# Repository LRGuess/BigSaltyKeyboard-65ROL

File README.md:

# BigSaltyKeyboard-65ROL
A 65% Keyboard with a rotary encoder, OLED screen and LEDs

## BOM:

- 1x Raspberry Pi Pico
- 68x Cheery MX Switches and their keycaps
- 68x [1N4148 Through-Hole Diodes](https://www.digikey.ca/en/products/detail/onsemi/1N4148/458603)
- 1x 6.25u Stabilizer
- 2x 2.25u Stabilizer
- 1x 2u Stabilizer
- 68x [SK6812 MINI-E LEDs](https://www.lcsc.com/product-detail/C5149201.html)
- 1x [Logic Level Shifter](https://www.digikey.ca/en/products/detail/texas-instruments/SN74AHCT1G125DBVR/376028)
- 69x [0.1 µF Chip Capacitor](https://www.digikey.ca/en/products/detail/samsung-electro-mechanics/CL05B104KP5VPNC/20498482)
- 1x [500 OHM Chip Resistor](https://www.digikey.ca/en/products/detail/yageo/RT0603BRC07500RL/7708292)
- 2x [10 Pin Horizontal Header](https://www.digikey.ca/en/products/detail/w%C3%BCrth-elektronik/61301011021/2508443)

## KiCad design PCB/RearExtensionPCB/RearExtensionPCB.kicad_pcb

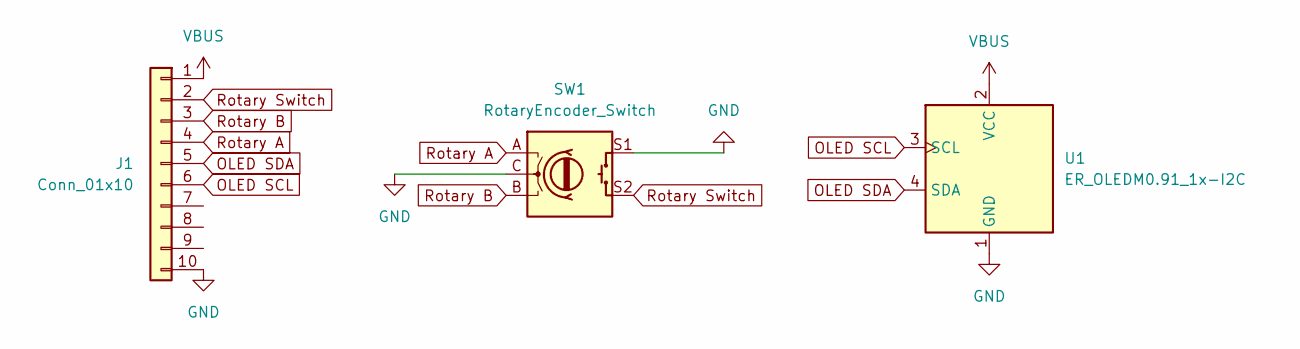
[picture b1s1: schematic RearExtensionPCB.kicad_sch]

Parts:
J1: Conn_01x10; PinHeader_1x10_P2.54mm_Horizontal
SW1: RotaryEncoder_Switch; RotaryEncoder_Alps_EC11E-Switch_Vertical_H20mm
U1: ER_OLEDM0.91_1x-I2C

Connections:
GND: J1.10, SW1.C, SW1.S1, U1.1 (GND)
OLED SCL: J1.6, U1.3 (SCL)
OLED SDA: J1.5, U1.4 (SDA)
Rotary A: J1.4, SW1.A
Rotary B: J1.3, SW1.B
Rotary Switch: J1.2, SW1.S2
VBUS: J1.1, U1.2 (VCC)

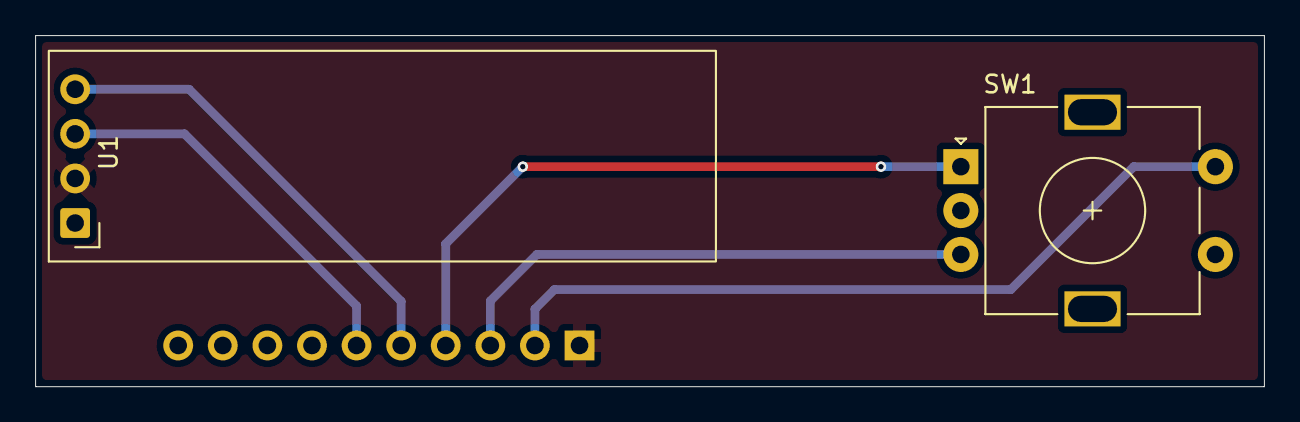
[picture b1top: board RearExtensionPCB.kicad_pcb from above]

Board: 2 copper layers, 70.0 x 20.0 mm, 3 parts (1 on the bottom side), 7 nets.

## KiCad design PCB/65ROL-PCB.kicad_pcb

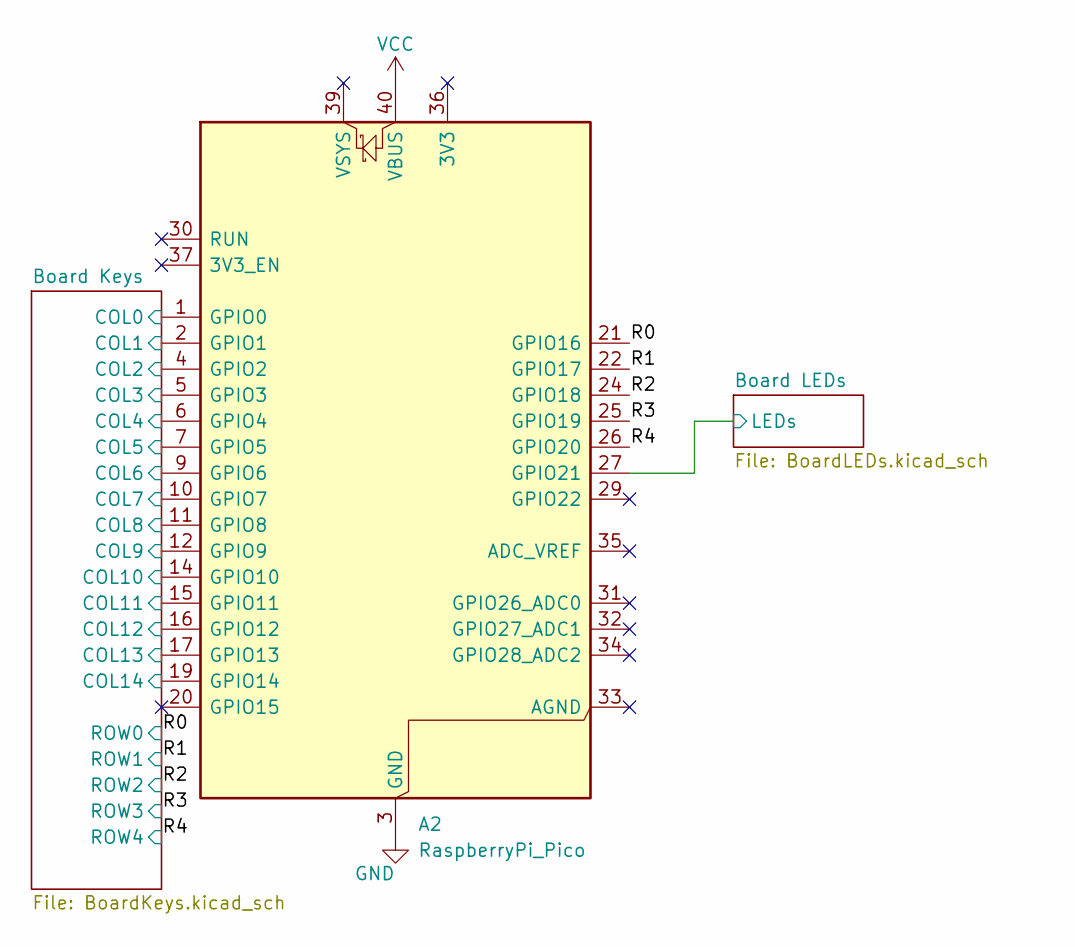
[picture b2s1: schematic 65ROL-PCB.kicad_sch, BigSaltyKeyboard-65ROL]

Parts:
A2: RaspberryPi_Pico; RaspberryPi_Pico_Common_THT

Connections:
/Board Keys/COL0: A2.1 (GPIO0); also elsewhere on the board
/Board Keys/COL1: A2.2 (GPIO1); also elsewhere on the board
/Board Keys/COL2: A2.4 (GPIO2); also elsewhere on the board
/Board Keys/COL3: A2.5 (GPIO3); also elsewhere on the board
/Board Keys/COL4: A2.6 (GPIO4); also elsewhere on the board
/Board Keys/COL5: A2.7 (GPIO5); also elsewhere on the board
/Board Keys/COL6: A2.9 (GPIO6); also elsewhere on the board
/Board Keys/COL7: A2.10 (GPIO7); also elsewhere on the board
/Board Keys/COL8: A2.11 (GPIO8); also elsewhere on the board
/Board Keys/COL9: A2.12 (GPIO9); also elsewhere on the board
/Board Keys/COL10: A2.14 (GPIO10); also elsewhere on the board
/Board Keys/COL11: A2.15 (GPIO11); also elsewhere on the board
/Board Keys/COL12: A2.16 (GPIO12); also elsewhere on the board
/Board Keys/COL13: A2.17 (GPIO13); also elsewhere on the board
/Board Keys/COL14: A2.19 (GPIO14); also elsewhere on the board
/Board LEDs/LEDs: A2.27 (GPIO21); also elsewhere on the board
/R0: A2.21 (GPIO16); also elsewhere on the board
/R1: A2.22 (GPIO17); also elsewhere on the board
/R2: A2.24 (GPIO18); also elsewhere on the board
/R3: A2.25 (GPIO19); also elsewhere on the board
/R4: A2.26 (GPIO20); also elsewhere on the board
GND: A2.3 (GND), A2.8 (GND), A2.13 (GND), A2.18 (GND), A2.23 (GND), A2.28 (GND), A2.38 (GND); also elsewhere on the board
VCC: A2.40 (VBUS); also elsewhere on the board

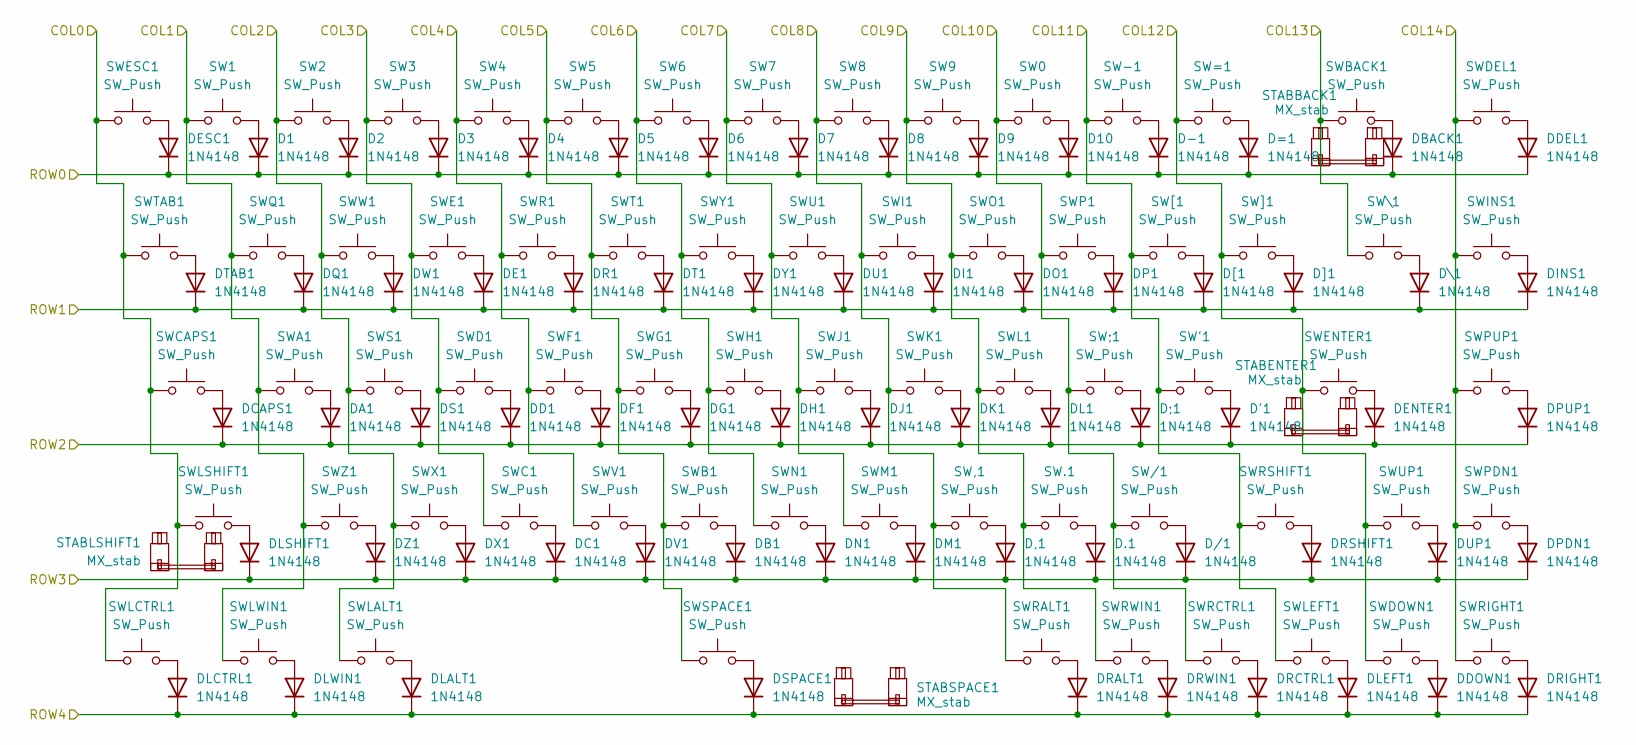
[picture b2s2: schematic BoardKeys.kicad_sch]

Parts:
D1, D2, D3, D4, D5, D6, D7, D8, D9, D10, D.1: 1N4148; D_DO-35_SOD27_P7.62mm_Horizontal
D'1: 1N4148; D_DO-35_SOD27_P7.62mm_Horizontal
D,1: 1N4148; D_DO-35_SOD27_P7.62mm_Horizontal
D-1: 1N4148; D_DO-35_SOD27_P7.62mm_Horizontal
D/1: 1N4148; D_DO-35_SOD27_P7.62mm_Horizontal
D;1: 1N4148; D_DO-35_SOD27_P7.62mm_Horizontal
D=1: 1N4148; D_DO-35_SOD27_P7.62mm_Horizontal
DA1: 1N4148; D_DO-35_SOD27_P7.62mm_Horizontal
DB1: 1N4148; D_DO-35_SOD27_P7.62mm_Horizontal
DBACK1: 1N4148; D_DO-35_SOD27_P7.62mm_Horizontal
DC1: 1N4148; D_DO-35_SOD27_P7.62mm_Horizontal
DCAPS1: 1N4148; D_DO-35_SOD27_P7.62mm_Horizontal
DD1: 1N4148; D_DO-35_SOD27_P7.62mm_Horizontal
DDEL1: 1N4148; D_DO-35_SOD27_P7.62mm_Horizontal
DDOWN1: 1N4148; D_DO-35_SOD27_P7.62mm_Horizontal
DE1: 1N4148; D_DO-35_SOD27_P7.62mm_Horizontal
DENTER1: 1N4148; D_DO-35_SOD27_P7.62mm_Horizontal
DESC1: 1N4148; D_DO-35_SOD27_P7.62mm_Horizontal
DF1: 1N4148; D_DO-35_SOD27_P7.62mm_Horizontal
DG1: 1N4148; D_DO-35_SOD27_P7.62mm_Horizontal
DH1: 1N4148; D_DO-35_SOD27_P7.62mm_Horizontal
DI1: 1N4148; D_DO-35_SOD27_P7.62mm_Horizontal
DINS1: 1N4148; D_DO-35_SOD27_P7.62mm_Horizontal
DJ1: 1N4148; D_DO-35_SOD27_P7.62mm_Horizontal
DK1: 1N4148; D_DO-35_SOD27_P7.62mm_Horizontal
DL1: 1N4148; D_DO-35_SOD27_P7.62mm_Horizontal
DLALT1: 1N4148; D_DO-35_SOD27_P7.62mm_Horizontal
DLCTRL1: 1N4148; D_DO-35_SOD27_P7.62mm_Horizontal
DLEFT1: 1N4148; D_DO-35_SOD27_P7.62mm_Horizontal
DLSHIFT1: 1N4148; D_DO-35_SOD27_P7.62mm_Horizontal
DLWIN1: 1N4148; D_DO-35_SOD27_P7.62mm_Horizontal
DM1: 1N4148; D_DO-35_SOD27_P7.62mm_Horizontal
DN1: 1N4148; D_DO-35_SOD27_P7.62mm_Horizontal
DO1: 1N4148; D_DO-35_SOD27_P7.62mm_Horizontal
DP1: 1N4148; D_DO-35_SOD27_P7.62mm_Horizontal
DPDN1: 1N4148; D_DO-35_SOD27_P7.62mm_Horizontal
DPUP1: 1N4148; D_DO-35_SOD27_P7.62mm_Horizontal
DQ1: 1N4148; D_DO-35_SOD27_P7.62mm_Horizontal
DR1: 1N4148; D_DO-35_SOD27_P7.62mm_Horizontal
DRALT1: 1N4148; D_DO-35_SOD27_P7.62mm_Horizontal
DRCTRL1: 1N4148; D_DO-35_SOD27_P7.62mm_Horizontal
DRIGHT1: 1N4148; D_DO-35_SOD27_P7.62mm_Horizontal
DRSHIFT1: 1N4148; D_DO-35_SOD27_P7.62mm_Horizontal
DRWIN1: 1N4148; D_DO-35_SOD27_P7.62mm_Horizontal
DS1: 1N4148; D_DO-35_SOD27_P7.62mm_Horizontal
DSPACE1: 1N4148; D_DO-35_SOD27_P7.62mm_Horizontal
DT1: 1N4148; D_DO-35_SOD27_P7.62mm_Horizontal
DTAB1: 1N4148; D_DO-35_SOD27_P7.62mm_Horizontal
DU1: 1N4148; D_DO-35_SOD27_P7.62mm_Horizontal
DUP1: 1N4148; D_DO-35_SOD27_P7.62mm_Horizontal
DV1: 1N4148; D_DO-35_SOD27_P7.62mm_Horizontal
DW1: 1N4148; D_DO-35_SOD27_P7.62mm_Horizontal
DX1: 1N4148; D_DO-35_SOD27_P7.62mm_Horizontal
DY1: 1N4148; D_DO-35_SOD27_P7.62mm_Horizontal
DZ1: 1N4148; D_DO-35_SOD27_P7.62mm_Horizontal
D[1: 1N4148; D_DO-35_SOD27_P7.62mm_Horizontal
D\1: 1N4148; D_DO-35_SOD27_P7.62mm_Horizontal
D]1: 1N4148; D_DO-35_SOD27_P7.62mm_Horizontal
STABBACK1: MX_stab; STAB_MX_2u
STABENTER1: MX_stab; STAB_MX_2.25u
STABLSHIFT1: MX_stab; STAB_MX_2.25u
STABSPACE1: MX_stab; STAB_MX_6.25u
SW0, SW1, SW2, SW3, SW4, SW5, SW6, SW7, SW8, SW9, SW.1: SW_Push; SW_MX_1u
SW'1: SW_Push; SW_MX_1u
SW,1: SW_Push; SW_MX_1u
SW-1: SW_Push; SW_MX_1u
SW/1: SW_Push; SW_MX_1u
SW;1: SW_Push; SW_MX_1u
SW=1: SW_Push; SW_MX_1u
SWA1: SW_Push; SW_MX_1u
SWB1: SW_Push; SW_MX_1u
SWBACK1: SW_Push; SW_MX_1u
SWC1: SW_Push; SW_MX_1u
SWCAPS1: SW_Push; SW_MX_1u
SWD1: SW_Push; SW_MX_1u
SWDEL1: SW_Push; SW_MX_1u
SWDOWN1: SW_Push; SW_MX_1u
SWE1: SW_Push; SW_MX_1u
SWENTER1: SW_Push; SW_MX_1u
SWESC1: SW_Push; SW_MX_1u
SWF1: SW_Push; SW_MX_1u
SWG1: SW_Push; SW_MX_1u
SWH1: SW_Push; SW_MX_1u
SWI1: SW_Push; SW_MX_1u
SWINS1: SW_Push; SW_MX_1u
SWJ1: SW_Push; SW_MX_1u
SWK1: SW_Push; SW_MX_1u
SWL1: SW_Push; SW_MX_1u
SWLALT1: SW_Push; SW_MX_1u
SWLCTRL1: SW_Push; SW_MX_1u
SWLEFT1: SW_Push; SW_MX_1u
SWLSHIFT1: SW_Push; SW_MX_1u
SWLWIN1: SW_Push; SW_MX_1u
SWM1: SW_Push; SW_MX_1u
SWN1: SW_Push; SW_MX_1u
SWO1: SW_Push; SW_MX_1u
SWP1: SW_Push; SW_MX_1u
SWPDN1: SW_Push; SW_MX_1u
SWPUP1: SW_Push; SW_MX_1u
SWQ1: SW_Push; SW_MX_1u
SWR1: SW_Push; SW_MX_1u
SWRALT1: SW_Push; SW_MX_1u
SWRCTRL1: SW_Push; SW_MX_1u
SWRIGHT1: SW_Push; SW_MX_1u
SWRSHIFT1: SW_Push; SW_MX_1u
SWRWIN1: SW_Push; SW_MX_1u
SWS1: SW_Push; SW_MX_1u
SWSPACE1: SW_Push; SW_MX_1u
SWT1: SW_Push; SW_MX_1u
SWTAB1: SW_Push; SW_MX_1u
SWU1: SW_Push; SW_MX_1u
SWUP1: SW_Push; SW_MX_1u
SWV1: SW_Push; SW_MX_1u
SWW1: SW_Push; SW_MX_1u
SWX1: SW_Push; SW_MX_1u
SWY1: SW_Push; SW_MX_1u
SWZ1: SW_Push; SW_MX_1u
SW[1: SW_Push; SW_MX_1u
SW\1: SW_Push; SW_MX_1u
SW]1: SW_Push; SW_MX_1u

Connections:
/Board Keys/COL0: SWCAPS1.1, SWESC1.1, SWLCTRL1.1, SWLSHIFT1.1, SWTAB1.1; also elsewhere on the board
/Board Keys/COL1: SW1.1, SWA1.1, SWLWIN1.1, SWQ1.1, SWZ1.1; also elsewhere on the board
/Board Keys/COL2: SW2.1, SWLALT1.1, SWS1.1, SWW1.1, SWX1.1; also elsewhere on the board
/Board Keys/COL3: SW3.1, SWC1.1, SWD1.1, SWE1.1; also elsewhere on the board
/Board Keys/COL4: SW4.1, SWF1.1, SWR1.1, SWV1.1; also elsewhere on the board
/Board Keys/COL5: SW5.1, SWB1.1, SWG1.1, SWSPACE1.1, SWT1.1; also elsewhere on the board
/Board Keys/COL6: SW6.1, SWH1.1, SWN1.1, SWY1.1; also elsewhere on the board
/Board Keys/COL7: SW7.1, SWJ1.1, SWM1.1, SWU1.1; also elsewhere on the board
/Board Keys/COL8: SW8.1, SW,1.1, SWI1.1, SWK1.1, SWRALT1.1; also elsewhere on the board
/Board Keys/COL9: SW9.1, SW.1.1, SWL1.1, SWO1.1, SWRWIN1.1; also elsewhere on the board
/Board Keys/COL10: SW0.1, SW/1.1, SW;1.1, SWP1.1, SWRCTRL1.1; also elsewhere on the board
/Board Keys/COL11: SW'1.1, SW-1.1, SWLEFT1.1, SWRSHIFT1.1, SW[1.1; also elsewhere on the board
/Board Keys/COL12: SW=1.1, SWDOWN1.1, SWENTER1.1, SWUP1.1, SW]1.1; also elsewhere on the board
/Board Keys/COL13: SWBACK1.1, SW\1.1; also elsewhere on the board
/Board Keys/COL14: SWDEL1.1, SWINS1.1, SWPDN1.1, SWPUP1.1, SWRIGHT1.1; also elsewhere on the board
/R0: D1.1 (K), D2.1 (K), D3.1 (K), D4.1 (K), D5.1 (K), D6.1 (K), D7.1 (K), D8.1 (K), D9.1 (K), D10.1 (K), D-1.1 (K), D=1.1 (K), DBACK1.1 (K), DDEL1.1 (K), DESC1.1 (K); also elsewhere on the board
/R1: DE1.1 (K), DI1.1 (K), DINS1.1 (K), DO1.1 (K), DP1.1 (K), DQ1.1 (K), DR1.1 (K), DT1.1 (K), DTAB1.1 (K), DU1.1 (K), DW1.1 (K), DY1.1 (K), D[1.1 (K), D\1.1 (K), D]1.1 (K); also elsewhere on the board
/R2: D'1.1 (K), D;1.1 (K), DA1.1 (K), DCAPS1.1 (K), DD1.1 (K), DENTER1.1 (K), DF1.1 (K), DG1.1 (K), DH1.1 (K), DJ1.1 (K), DK1.1 (K), DL1.1 (K), DPUP1.1 (K), DS1.1 (K); also elsewhere on the board
/R3: D,1.1 (K), D.1.1 (K), D/1.1 (K), DB1.1 (K), DC1.1 (K), DLSHIFT1.1 (K), DM1.1 (K), DN1.1 (K), DPDN1.1 (K), DRSHIFT1.1 (K), DUP1.1 (K), DV1.1 (K), DX1.1 (K), DZ1.1 (K); also elsewhere on the board
/R4: DDOWN1.1 (K), DLALT1.1 (K), DLCTRL1.1 (K), DLEFT1.1 (K), DLWIN1.1 (K), DRALT1.1 (K), DRCTRL1.1 (K), DRIGHT1.1 (K), DRWIN1.1 (K), DSPACE1.1 (K); also elsewhere on the board
unnamed: D1.2 (A), SW1.2
unnamed: D2.2 (A), SW2.2
unnamed: D3.2 (A), SW3.2
unnamed: D4.2 (A), SW4.2
unnamed: D5.2 (A), SW5.2
unnamed: D6.2 (A), SW6.2
unnamed: D7.2 (A), SW7.2
unnamed: D8.2 (A), SW8.2
unnamed: D9.2 (A), SW9.2
unnamed: D10.2 (A), SW0.2
unnamed: D'1.2 (A), SW'1.2
unnamed: D,1.2 (A), SW,1.2
unnamed: D-1.2 (A), SW-1.2
unnamed: D.1.2 (A), SW.1.2
unnamed: D/1.2 (A), SW/1.2
unnamed: D;1.2 (A), SW;1.2
unnamed: D=1.2 (A), SW=1.2
unnamed: DA1.2 (A), SWA1.2
unnamed: DB1.2 (A), SWB1.2
unnamed: DBACK1.2 (A), SWBACK1.2
unnamed: DC1.2 (A), SWC1.2
unnamed: DCAPS1.2 (A), SWCAPS1.2
unnamed: DD1.2 (A), SWD1.2
unnamed: DDEL1.2 (A), SWDEL1.2
unnamed: DDOWN1.2 (A), SWDOWN1.2
unnamed: DE1.2 (A), SWE1.2
unnamed: DENTER1.2 (A), SWENTER1.2
unnamed: DESC1.2 (A), SWESC1.2
unnamed: DF1.2 (A), SWF1.2
unnamed: DG1.2 (A), SWG1.2
unnamed: DH1.2 (A), SWH1.2
unnamed: DI1.2 (A), SWI1.2
unnamed: DINS1.2 (A), SWINS1.2
unnamed: DJ1.2 (A), SWJ1.2
unnamed: DK1.2 (A), SWK1.2
unnamed: DL1.2 (A), SWL1.2
unnamed: DLALT1.2 (A), SWLALT1.2
unnamed: DLCTRL1.2 (A), SWLCTRL1.2
unnamed: DLEFT1.2 (A), SWLEFT1.2
unnamed: DLSHIFT1.2 (A), SWLSHIFT1.2
unnamed: DLWIN1.2 (A), SWLWIN1.2
unnamed: DM1.2 (A), SWM1.2
unnamed: DN1.2 (A), SWN1.2
unnamed: DO1.2 (A), SWO1.2
unnamed: DP1.2 (A), SWP1.2
unnamed: DPDN1.2 (A), SWPDN1.2
unnamed: DPUP1.2 (A), SWPUP1.2
unnamed: DQ1.2 (A), SWQ1.2
unnamed: DR1.2 (A), SWR1.2
unnamed: DRALT1.2 (A), SWRALT1.2
unnamed: DRCTRL1.2 (A), SWRCTRL1.2
unnamed: DRIGHT1.2 (A), SWRIGHT1.2
unnamed: DRSHIFT1.2 (A), SWRSHIFT1.2
unnamed: DRWIN1.2 (A), SWRWIN1.2
unnamed: DS1.2 (A), SWS1.2
unnamed: DSPACE1.2 (A), SWSPACE1.2
unnamed: DT1.2 (A), SWT1.2
unnamed: DTAB1.2 (A), SWTAB1.2
unnamed: DU1.2 (A), SWU1.2
unnamed: DUP1.2 (A), SWUP1.2
unnamed: DV1.2 (A), SWV1.2
unnamed: DW1.2 (A), SWW1.2
unnamed: DX1.2 (A), SWX1.2
unnamed: DY1.2 (A), SWY1.2
unnamed: DZ1.2 (A), SWZ1.2
unnamed: D[1.2 (A), SW[1.2
unnamed: D\1.2 (A), SW\1.2
unnamed: D]1.2 (A), SW]1.2

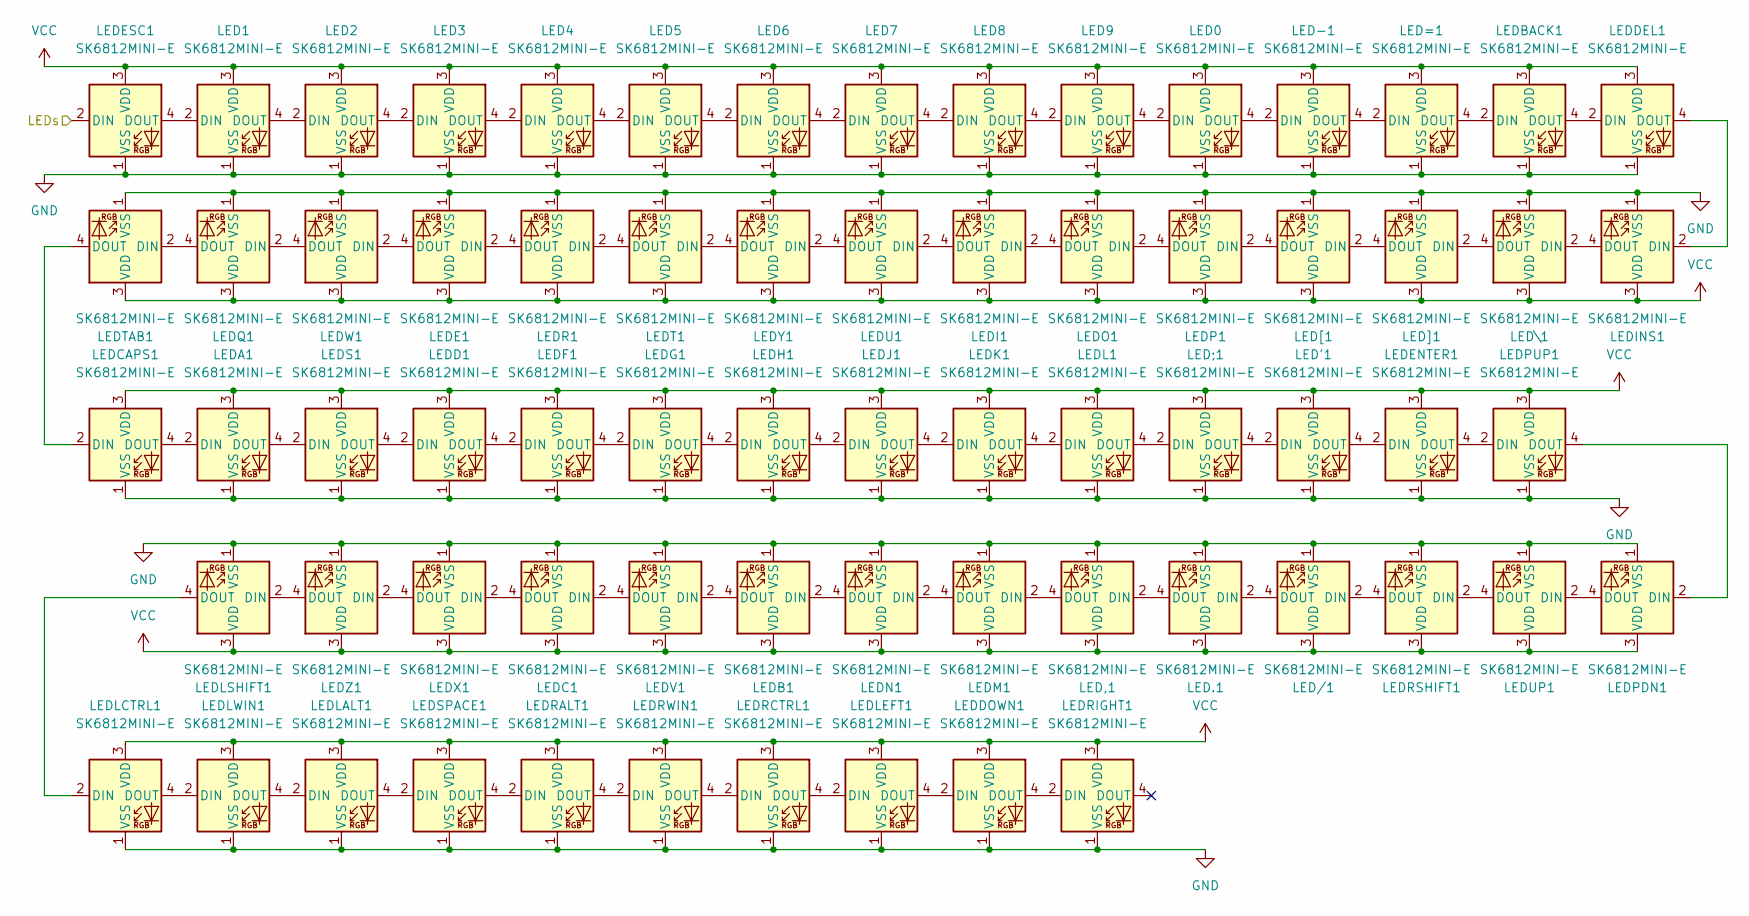
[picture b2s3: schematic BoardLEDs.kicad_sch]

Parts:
LED0, LED1, LED2, LED3, LED4, LED5, LED6, LED7, LED8, LED9, LED.1: SK6812MINI-E; SK6812MINI-E_fixed
LED'1: SK6812MINI-E; SK6812MINI-E_fixed
LED,1: SK6812MINI-E; SK6812MINI-E_fixed
LED-1: SK6812MINI-E; SK6812MINI-E_fixed
LED/1: SK6812MINI-E; SK6812MINI-E_fixed
LED;1: SK6812MINI-E; SK6812MINI-E_fixed
LED=1: SK6812MINI-E; SK6812MINI-E_fixed
LEDA1: SK6812MINI-E; SK6812MINI-E_fixed
LEDB1: SK6812MINI-E; SK6812MINI-E_fixed
LEDBACK1: SK6812MINI-E; SK6812MINI-E_fixed
LEDC1: SK6812MINI-E; SK6812MINI-E_fixed
LEDCAPS1: SK6812MINI-E; SK6812MINI-E_fixed
LEDD1: SK6812MINI-E; SK6812MINI-E_fixed
LEDDEL1: SK6812MINI-E; SK6812MINI-E_fixed
LEDDOWN1: SK6812MINI-E; SK6812MINI-E_fixed
LEDE1: SK6812MINI-E; SK6812MINI-E_fixed
LEDENTER1: SK6812MINI-E; SK6812MINI-E_fixed
LEDESC1: SK6812MINI-E; SK6812MINI-E_fixed
LEDF1: SK6812MINI-E; SK6812MINI-E_fixed
LEDG1: SK6812MINI-E; SK6812MINI-E_fixed
LEDH1: SK6812MINI-E; SK6812MINI-E_fixed
LEDI1: SK6812MINI-E; SK6812MINI-E_fixed
LEDINS1: SK6812MINI-E; SK6812MINI-E_fixed
LEDJ1: SK6812MINI-E; SK6812MINI-E_fixed
LEDK1: SK6812MINI-E; SK6812MINI-E_fixed
LEDL1: SK6812MINI-E; SK6812MINI-E_fixed
LEDLALT1: SK6812MINI-E; SK6812MINI-E_fixed
LEDLCTRL1: SK6812MINI-E; SK6812MINI-E_fixed
LEDLEFT1: SK6812MINI-E; SK6812MINI-E_fixed
LEDLSHIFT1: SK6812MINI-E; SK6812MINI-E_fixed
LEDLWIN1: SK6812MINI-E; SK6812MINI-E_fixed
LEDM1: SK6812MINI-E; SK6812MINI-E_fixed
LEDN1: SK6812MINI-E; SK6812MINI-E_fixed
LEDO1: SK6812MINI-E; SK6812MINI-E_fixed
LEDP1: SK6812MINI-E; SK6812MINI-E_fixed
LEDPDN1: SK6812MINI-E; SK6812MINI-E_fixed
LEDPUP1: SK6812MINI-E; SK6812MINI-E_fixed
LEDQ1: SK6812MINI-E; SK6812MINI-E_fixed
LEDR1: SK6812MINI-E; SK6812MINI-E_fixed
LEDRALT1: SK6812MINI-E; SK6812MINI-E_fixed
LEDRCTRL1: SK6812MINI-E; SK6812MINI-E_fixed
LEDRIGHT1: SK6812MINI-E; SK6812MINI-E_fixed
LEDRSHIFT1: SK6812MINI-E; SK6812MINI-E_fixed
LEDRWIN1: SK6812MINI-E; SK6812MINI-E_fixed
LEDS1: SK6812MINI-E; SK6812MINI-E_fixed
LEDSPACE1: SK6812MINI-E; SK6812MINI-E_fixed
LEDT1: SK6812MINI-E; SK6812MINI-E_fixed
LEDTAB1: SK6812MINI-E; SK6812MINI-E_fixed
LEDU1: SK6812MINI-E; SK6812MINI-E_fixed
LEDUP1: SK6812MINI-E; SK6812MINI-E_fixed
LEDV1: SK6812MINI-E; SK6812MINI-E_fixed
LEDW1: SK6812MINI-E; SK6812MINI-E_fixed
LEDX1: SK6812MINI-E; SK6812MINI-E_fixed
LEDY1: SK6812MINI-E; SK6812MINI-E_fixed
LEDZ1: SK6812MINI-E; SK6812MINI-E_fixed
LED[1: SK6812MINI-E; SK6812MINI-E_fixed
LED\1: SK6812MINI-E; SK6812MINI-E_fixed
LED]1: SK6812MINI-E; SK6812MINI-E_fixed

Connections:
/Board LEDs/LEDs: LEDESC1.2 (DIN); also elsewhere on the board
GND: LED0.1 (VSS), LED1.1 (VSS), LED2.1 (VSS), LED3.1 (VSS), LED4.1 (VSS), LED5.1 (VSS), LED6.1 (VSS), LED7.1 (VSS), LED8.1 (VSS), LED9.1 (VSS), LED'1.1 (VSS), LED,1.1 (VSS), LED-1.1 (VSS), LED.1.1 (VSS), LED/1.1 (VSS), LED;1.1 (VSS), LED=1.1 (VSS), LEDA1.1 (VSS), LEDB1.1 (VSS), LEDBACK1.1 (VSS), LEDC1.1 (VSS), LEDCAPS1.1 (VSS), LEDD1.1 (VSS), LEDDEL1.1 (VSS), LEDDOWN1.1 (VSS), LEDE1.1 (VSS), LEDENTER1.1 (VSS), LEDESC1.1 (VSS), LEDF1.1 (VSS), LEDG1.1 (VSS), LEDH1.1 (VSS), LEDI1.1 (VSS), LEDINS1.1 (VSS), LEDJ1.1 (VSS), LEDK1.1 (VSS), LEDL1.1 (VSS), LEDLALT1.1 (VSS), LEDLCTRL1.1 (VSS), LEDLEFT1.1 (VSS), LEDLSHIFT1.1 (VSS), LEDLWIN1.1 (VSS), LEDM1.1 (VSS), LEDN1.1 (VSS), LEDO1.1 (VSS), LEDP1.1 (VSS), LEDPDN1.1 (VSS), LEDPUP1.1 (VSS), LEDQ1.1 (VSS), LEDR1.1 (VSS), LEDRALT1.1 (VSS), LEDRCTRL1.1 (VSS), LEDRIGHT1.1 (VSS), LEDRSHIFT1.1 (VSS), LEDRWIN1.1 (VSS), LEDS1.1 (VSS), LEDSPACE1.1 (VSS), LEDT1.1 (VSS), LEDTAB1.1 (VSS), LEDU1.1 (VSS), LEDUP1.1 (VSS), LEDV1.1 (VSS), LEDW1.1 (VSS), LEDX1.1 (VSS), LEDY1.1 (VSS), LEDZ1.1 (VSS), LED[1.1 (VSS), LED\1.1 (VSS), LED]1.1 (VSS); also elsewhere on the board
unnamed: LED0.2 (DIN), LED9.4 (DOUT)
unnamed: LED1.2 (DIN), LEDESC1.4 (DOUT)
unnamed: LED1.4 (DOUT), LED2.2 (DIN)
unnamed: LED2.4 (DOUT), LED3.2 (DIN)
unnamed: LED3.4 (DOUT), LED4.2 (DIN)
unnamed: LED4.4 (DOUT), LED5.2 (DIN)
unnamed: LED5.4 (DOUT), LED6.2 (DIN)
unnamed: LED6.4 (DOUT), LED7.2 (DIN)
unnamed: LED7.4 (DOUT), LED8.2 (DIN)
unnamed: LED8.4 (DOUT), LED9.2 (DIN)
unnamed: LED'1.2 (DIN), LED;1.4 (DOUT)
unnamed: LED'1.4 (DOUT), LEDENTER1.2 (DIN)
unnamed: LED,1.2 (DIN), LED.1.4 (DOUT)
unnamed: LED,1.4 (DOUT), LEDM1.2 (DIN)
unnamed: LED0.4 (DOUT), LED-1.2 (DIN)
unnamed: LED-1.4 (DOUT), LED=1.2 (DIN)
unnamed: LED.1.2 (DIN), LED/1.4 (DOUT)
unnamed: LED/1.2 (DIN), LEDRSHIFT1.4 (DOUT)
unnamed: LED;1.2 (DIN), LEDL1.4 (DOUT)
unnamed: LED=1.4 (DOUT), LEDBACK1.2 (DIN)
unnamed: LEDA1.2 (DIN), LEDCAPS1.4 (DOUT)
unnamed: LEDA1.4 (DOUT), LEDS1.2 (DIN)
unnamed: LEDB1.2 (DIN), LEDN1.4 (DOUT)
unnamed: LEDB1.4 (DOUT), LEDV1.2 (DIN)
unnamed: LEDBACK1.4 (DOUT), LEDDEL1.2 (DIN)
unnamed: LEDC1.2 (DIN), LEDV1.4 (DOUT)
unnamed: LEDC1.4 (DOUT), LEDX1.2 (DIN)
unnamed: LEDCAPS1.2 (DIN), LEDTAB1.4 (DOUT)
unnamed: LEDD1.2 (DIN), LEDS1.4 (DOUT)
unnamed: LEDD1.4 (DOUT), LEDF1.2 (DIN)
unnamed: LEDDEL1.4 (DOUT), LEDINS1.2 (DIN)
unnamed: LEDDOWN1.2 (DIN), LEDLEFT1.4 (DOUT)
unnamed: LEDDOWN1.4 (DOUT), LEDRIGHT1.2 (DIN)
unnamed: LEDE1.2 (DIN), LEDR1.4 (DOUT)
unnamed: LEDE1.4 (DOUT), LEDW1.2 (DIN)
unnamed: LEDENTER1.4 (DOUT), LEDPUP1.2 (DIN)
unnamed: LEDF1.4 (DOUT), LEDG1.2 (DIN)
unnamed: LEDG1.4 (DOUT), LEDH1.2 (DIN)
unnamed: LEDH1.4 (DOUT), LEDJ1.2 (DIN)
unnamed: LEDI1.2 (DIN), LEDO1.4 (DOUT)
unnamed: LEDI1.4 (DOUT), LEDU1.2 (DIN)
unnamed: LEDINS1.4 (DOUT), LED\1.2 (DIN)
unnamed: LEDJ1.4 (DOUT), LEDK1.2 (DIN)
unnamed: LEDK1.4 (DOUT), LEDL1.2 (DIN)
unnamed: LEDLALT1.2 (DIN), LEDLWIN1.4 (DOUT)
unnamed: LEDLALT1.4 (DOUT), LEDSPACE1.2 (DIN)
unnamed: LEDLCTRL1.2 (DIN), LEDLSHIFT1.4 (DOUT)
unnamed: LEDLCTRL1.4 (DOUT), LEDLWIN1.2 (DIN)
unnamed: LEDLEFT1.2 (DIN), LEDRCTRL1.4 (DOUT)
unnamed: LEDLSHIFT1.2 (DIN), LEDZ1.4 (DOUT)
unnamed: LEDM1.4 (DOUT), LEDN1.2 (DIN)
unnamed: LEDO1.2 (DIN), LEDP1.4 (DOUT)
unnamed: LEDP1.2 (DIN), LED[1.4 (DOUT)
unnamed: LEDPDN1.2 (DIN), LEDPUP1.4 (DOUT)
unnamed: LEDPDN1.4 (DOUT), LEDUP1.2 (DIN)
unnamed: LEDQ1.2 (DIN), LEDW1.4 (DOUT)
unnamed: LEDQ1.4 (DOUT), LEDTAB1.2 (DIN)
unnamed: LEDR1.2 (DIN), LEDT1.4 (DOUT)
unnamed: LEDRALT1.2 (DIN), LEDSPACE1.4 (DOUT)
unnamed: LEDRALT1.4 (DOUT), LEDRWIN1.2 (DIN)
unnamed: LEDRCTRL1.2 (DIN), LEDRWIN1.4 (DOUT)
unnamed: LEDRSHIFT1.2 (DIN), LEDUP1.4 (DOUT)
unnamed: LEDT1.2 (DIN), LEDY1.4 (DOUT)
unnamed: LEDU1.4 (DOUT), LEDY1.2 (DIN)
unnamed: LEDX1.4 (DOUT), LEDZ1.2 (DIN)
unnamed: LED[1.2 (DIN), LED]1.4 (DOUT)
unnamed: LED\1.4 (DOUT), LED]1.2 (DIN)
VCC: LED0.3 (VDD), LED1.3 (VDD), LED2.3 (VDD), LED3.3 (VDD), LED4.3 (VDD), LED5.3 (VDD), LED6.3 (VDD), LED7.3 (VDD), LED8.3 (VDD), LED9.3 (VDD), LED'1.3 (VDD), LED,1.3 (VDD), LED-1.3 (VDD), LED.1.3 (VDD), LED/1.3 (VDD), LED;1.3 (VDD), LED=1.3 (VDD), LEDA1.3 (VDD), LEDB1.3 (VDD), LEDBACK1.3 (VDD), LEDC1.3 (VDD), LEDCAPS1.3 (VDD), LEDD1.3 (VDD), LEDDEL1.3 (VDD), LEDDOWN1.3 (VDD), LEDE1.3 (VDD), LEDENTER1.3 (VDD), LEDESC1.3 (VDD), LEDF1.3 (VDD), LEDG1.3 (VDD), LEDH1.3 (VDD), LEDI1.3 (VDD), LEDINS1.3 (VDD), LEDJ1.3 (VDD), LEDK1.3 (VDD), LEDL1.3 (VDD), LEDLALT1.3 (VDD), LEDLCTRL1.3 (VDD), LEDLEFT1.3 (VDD), LEDLSHIFT1.3 (VDD), LEDLWIN1.3 (VDD), LEDM1.3 (VDD), LEDN1.3 (VDD), LEDO1.3 (VDD), LEDP1.3 (VDD), LEDPDN1.3 (VDD), LEDPUP1.3 (VDD), LEDQ1.3 (VDD), LEDR1.3 (VDD), LEDRALT1.3 (VDD), LEDRCTRL1.3 (VDD), LEDRIGHT1.3 (VDD), LEDRSHIFT1.3 (VDD), LEDRWIN1.3 (VDD), LEDS1.3 (VDD), LEDSPACE1.3 (VDD), LEDT1.3 (VDD), LEDTAB1.3 (VDD), LEDU1.3 (VDD), LEDUP1.3 (VDD), LEDV1.3 (VDD), LEDW1.3 (VDD), LEDX1.3 (VDD), LEDY1.3 (VDD), LEDZ1.3 (VDD), LED[1.3 (VDD), LED\1.3 (VDD), LED]1.3 (VDD); also elsewhere on the board

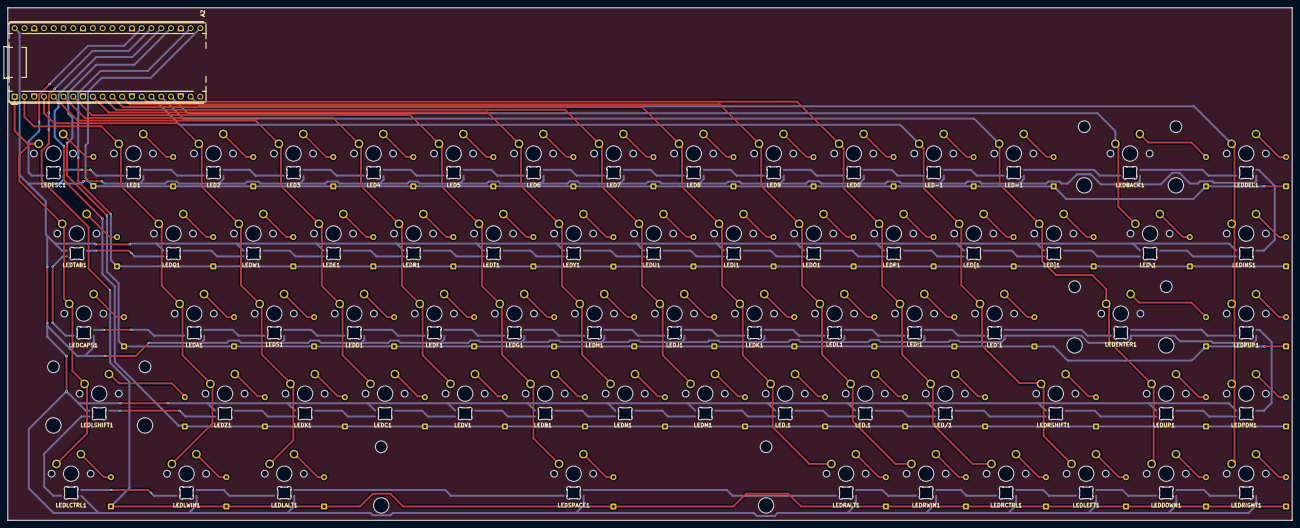
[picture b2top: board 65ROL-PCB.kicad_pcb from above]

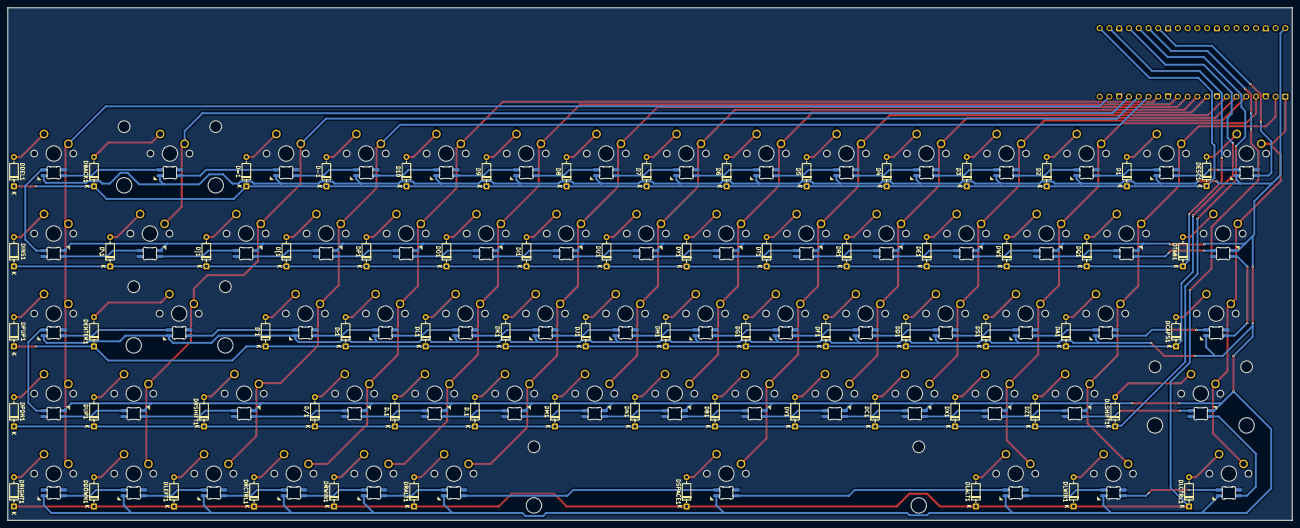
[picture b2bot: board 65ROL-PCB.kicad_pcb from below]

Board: 2 copper layers, 333.8 x 133.2 mm, 209 parts (68 on the bottom side), 158 nets.
